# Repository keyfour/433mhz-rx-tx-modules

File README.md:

## 433MHz RX/TX modules

### ArduinoUnoHat

Testboard for initial modules testing

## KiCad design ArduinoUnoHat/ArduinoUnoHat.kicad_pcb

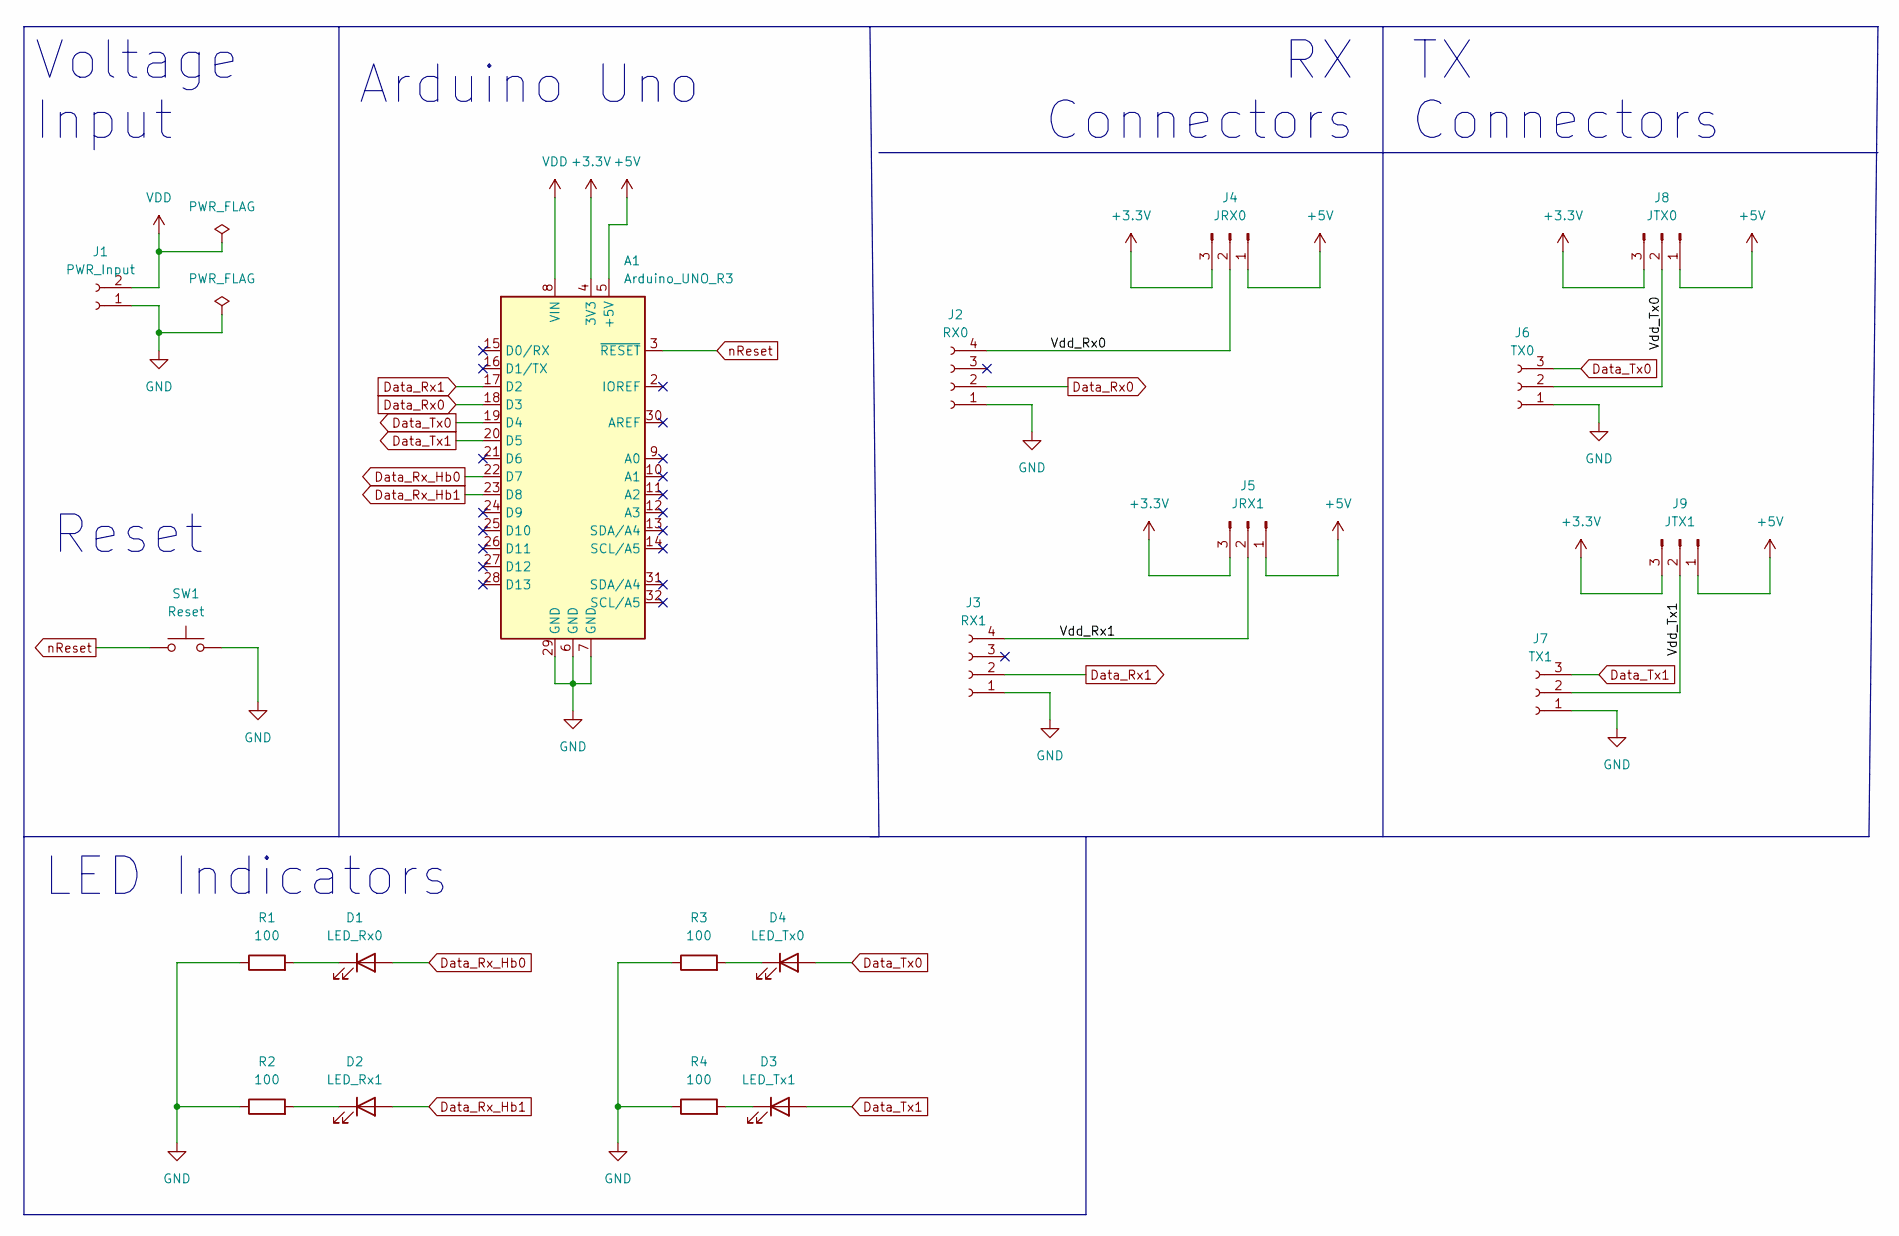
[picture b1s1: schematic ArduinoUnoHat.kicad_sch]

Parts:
A1: Arduino_UNO_R3
D1: LED_Rx0; LED_D5.0mm
D2: LED_Rx1; LED_D5.0mm
D3: LED_Tx1; LED_D5.0mm
D4: LED_Tx0; LED_D5.0mm
J1: PWR_Input; TerminalBlock_Altech_AK300-2_P5.00mm
J2: RX0; PinSocket_1x04_P2.54mm_Vertical
J3: RX1; PinSocket_1x04_P2.54mm_Horizontal
J4: JRX0; PinHeader_1x03_P2.54mm_Vertical
J5: JRX1; PinHeader_1x03_P2.54mm_Vertical
J6: TX0; PinSocket_1x03_P2.54mm_Vertical
J7: TX1; PinSocket_1x03_P2.54mm_Horizontal
J8: JTX0; PinHeader_1x03_P2.54mm_Vertical
J9: JTX1; PinHeader_1x03_P2.54mm_Vertical
R1, R2, R3, R4: 100; R_Axial_DIN0207_L6.3mm_D2.5mm_P10.16mm_Horizontal
SW1: Reset; SW_PUSH_6mm_H4.3mm

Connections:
+3.3V: A1.4 (3V3), J4.3, J5.3, J8.3, J9.3
+5V: A1.5 (+5V), J4.1, J5.1, J8.1, J9.1
/Vdd_Rx0: J2.4, J4.2
/Vdd_Rx1: J3.4, J5.2
/Vdd_Tx0: J6.2, J8.2
/Vdd_Tx1: J7.2, J9.2
Data_Rx0: A1.18 (D3), J2.2
Data_Rx1: A1.17 (D2), J3.2
Data_Rx_Hb0: A1.22 (D7), D1.2 (A)
Data_Rx_Hb1: A1.23 (D8), D2.2 (A)
Data_Tx0: A1.19 (D4), D4.2 (A), J6.3
Data_Tx1: A1.20 (D5), D3.2 (A), J7.3
GND: A1.6 (GND), A1.7 (GND), A1.29 (GND), J1.1, J2.1, J3.1, J6.1, J7.1, R1.1, R2.1, R3.1, R4.1, SW1.2
unnamed: D1.1 (K), R1.2
unnamed: D2.1 (K), R2.2
unnamed: D3.1 (K), R4.2
unnamed: D4.1 (K), R3.2
VDD: A1.8 (VIN), J1.2
nReset: A1.3 (~RESET), SW1.1

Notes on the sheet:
RX Connectors
TX Connectors
Arduino Uno
Reset
LED Indicators
Voltage Input

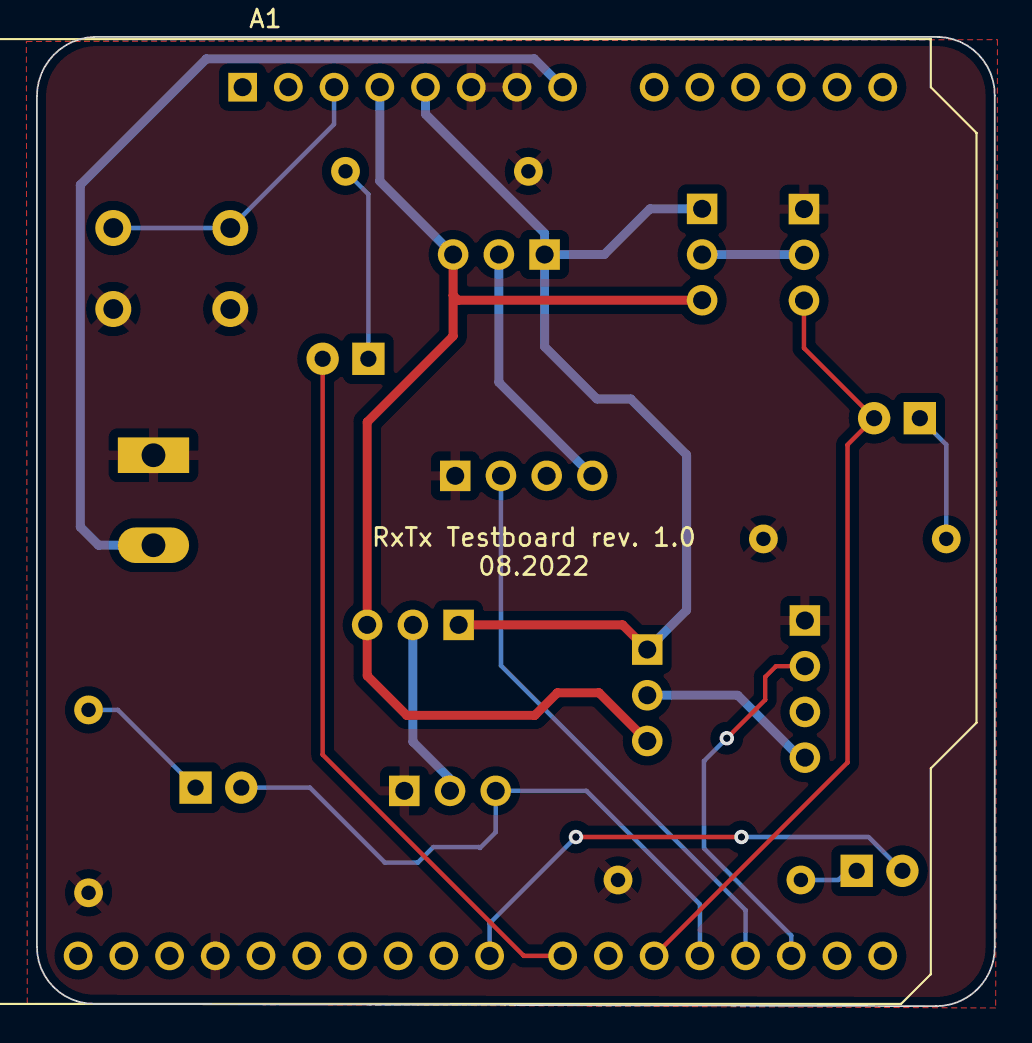
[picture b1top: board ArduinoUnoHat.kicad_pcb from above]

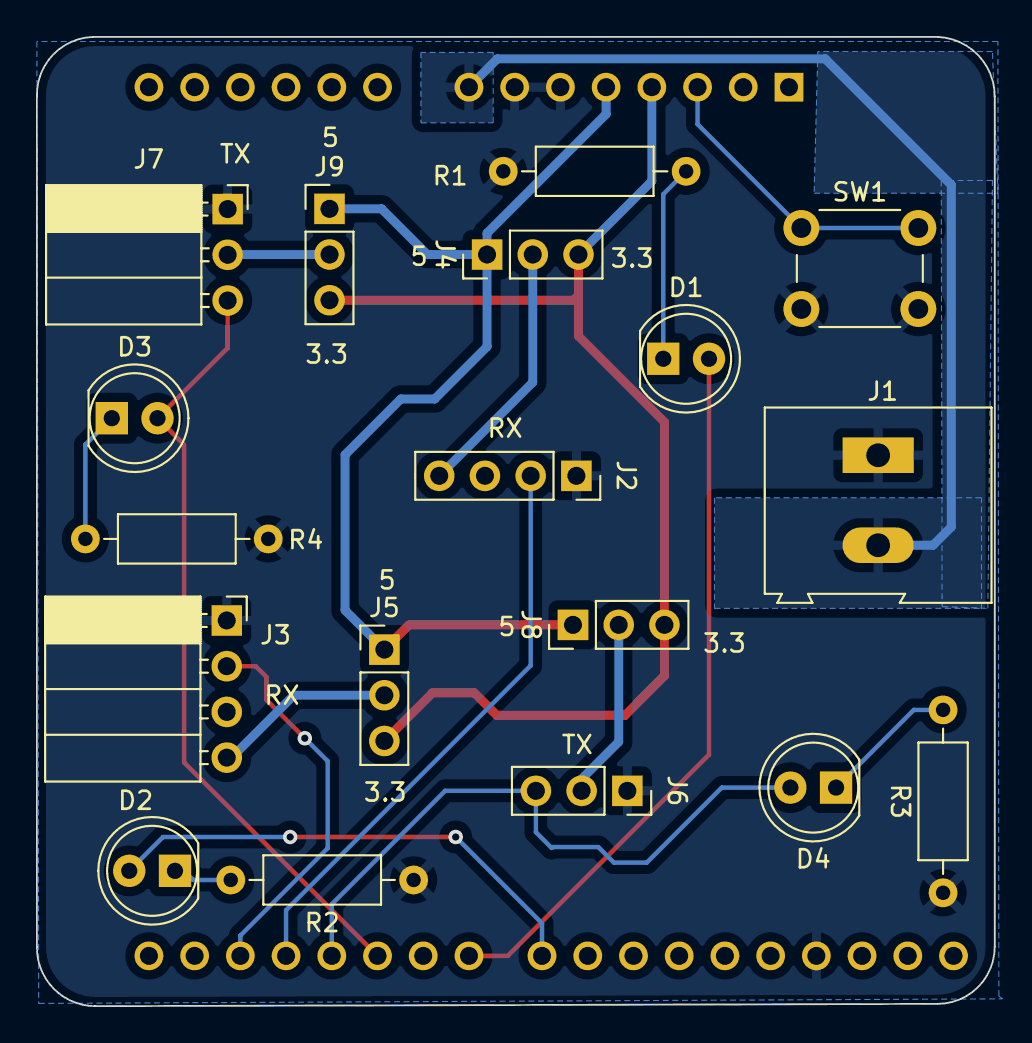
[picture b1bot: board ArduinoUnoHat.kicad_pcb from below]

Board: 2 copper layers, 53.2 x 53.8 mm, 19 parts (18 on the bottom side), 19 nets.

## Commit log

2022-08-21 Add readme
2022-08-21 Fix typo in the path
